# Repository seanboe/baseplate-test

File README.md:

# Baseplate test board

This is the baseplate test board for the Onyx baseplate. The schematic is mainly completed, but the layout isn't anywhere close to being finished. The board is based on the USB5537B 1-7 usb hub chip. 

Schematic:

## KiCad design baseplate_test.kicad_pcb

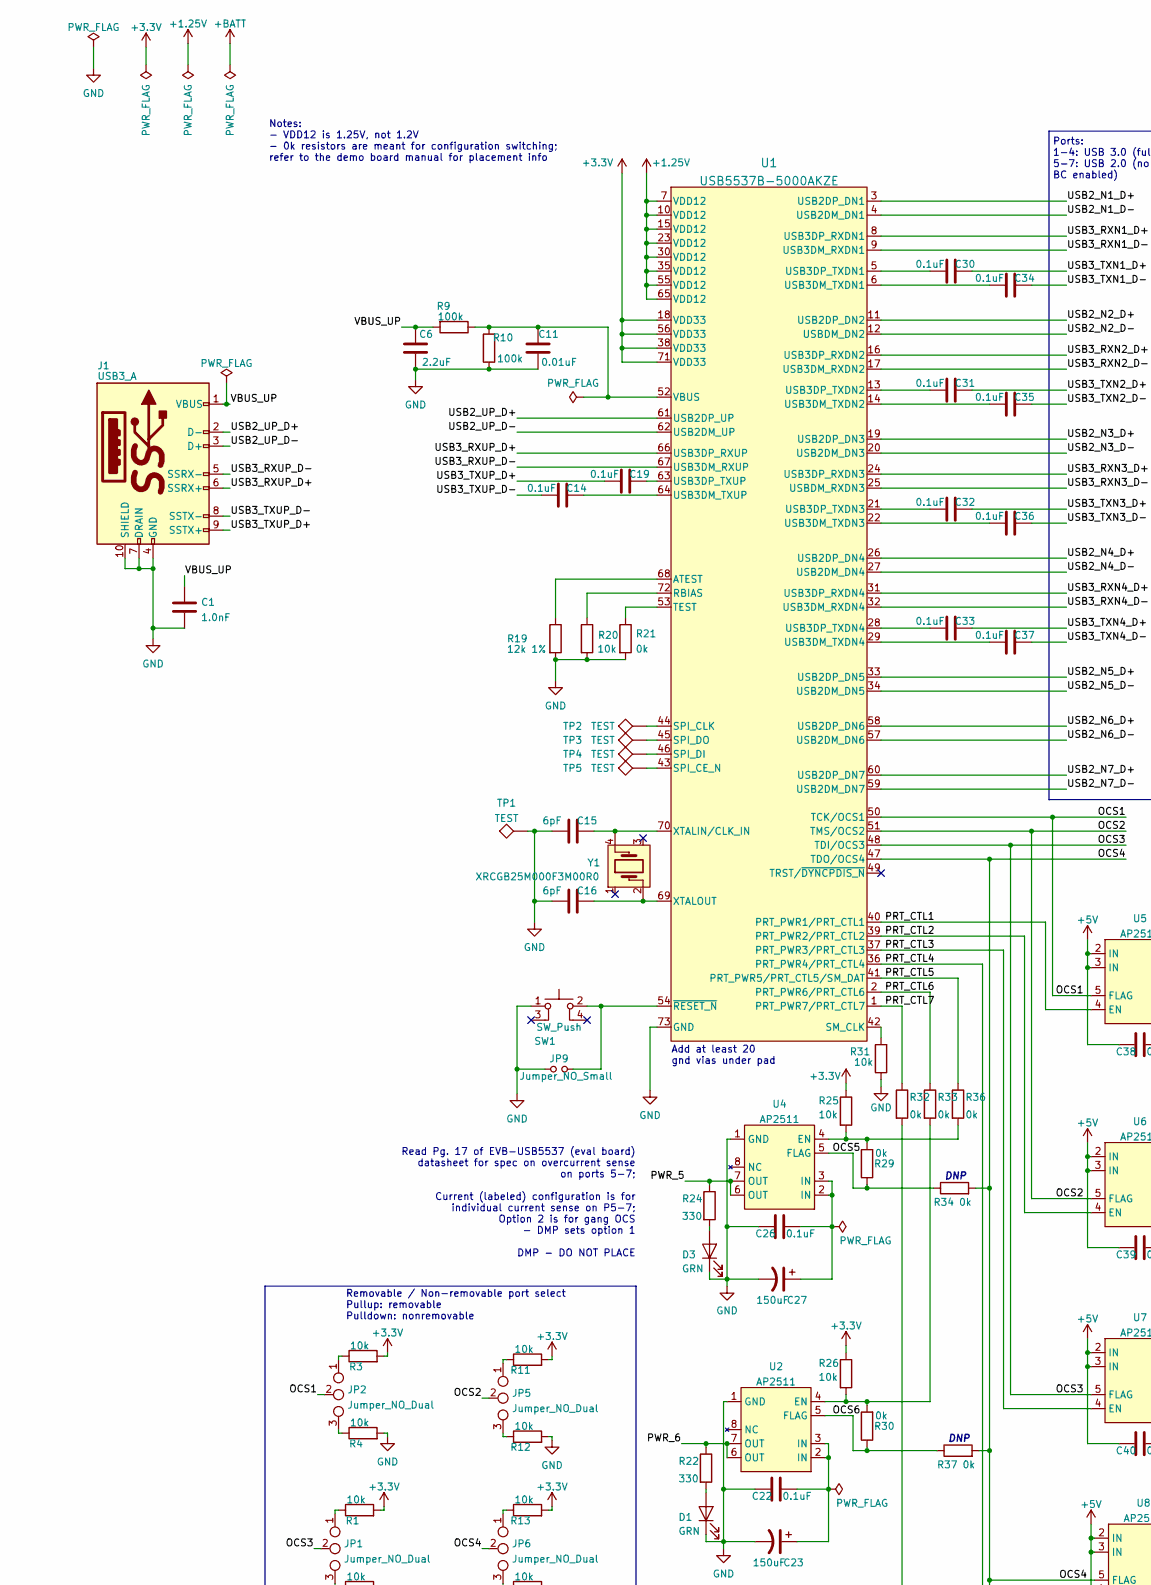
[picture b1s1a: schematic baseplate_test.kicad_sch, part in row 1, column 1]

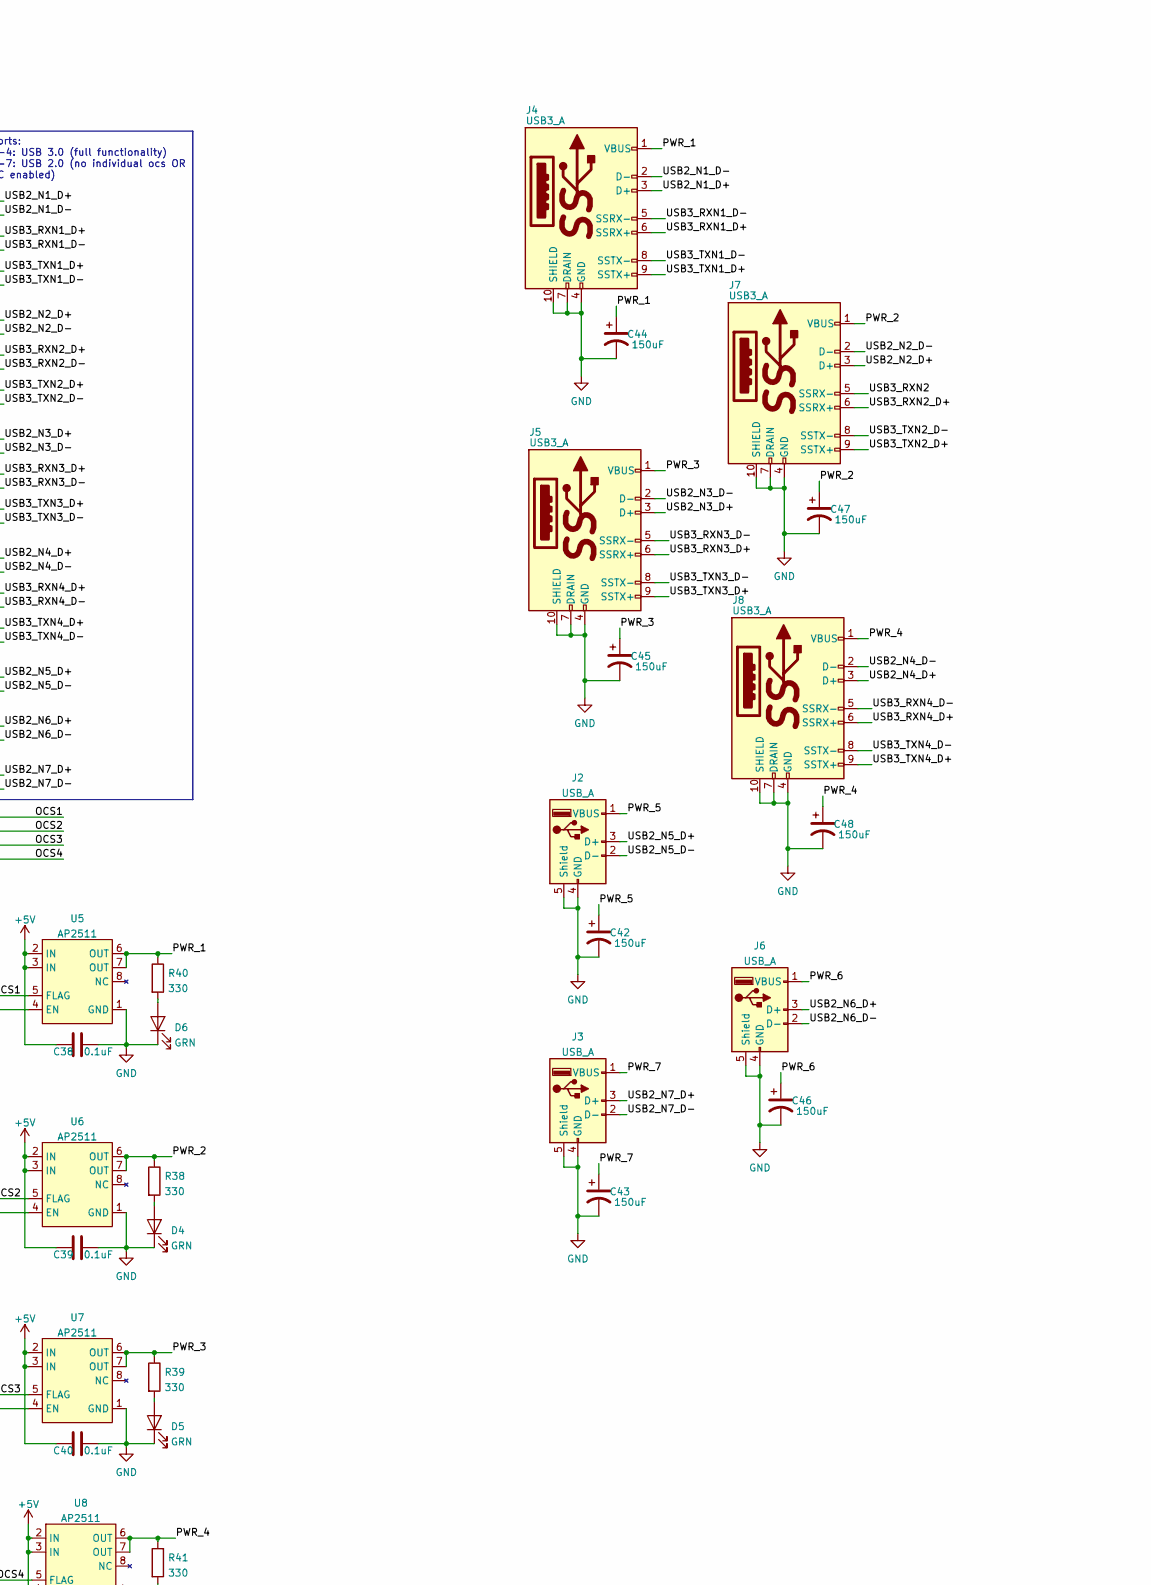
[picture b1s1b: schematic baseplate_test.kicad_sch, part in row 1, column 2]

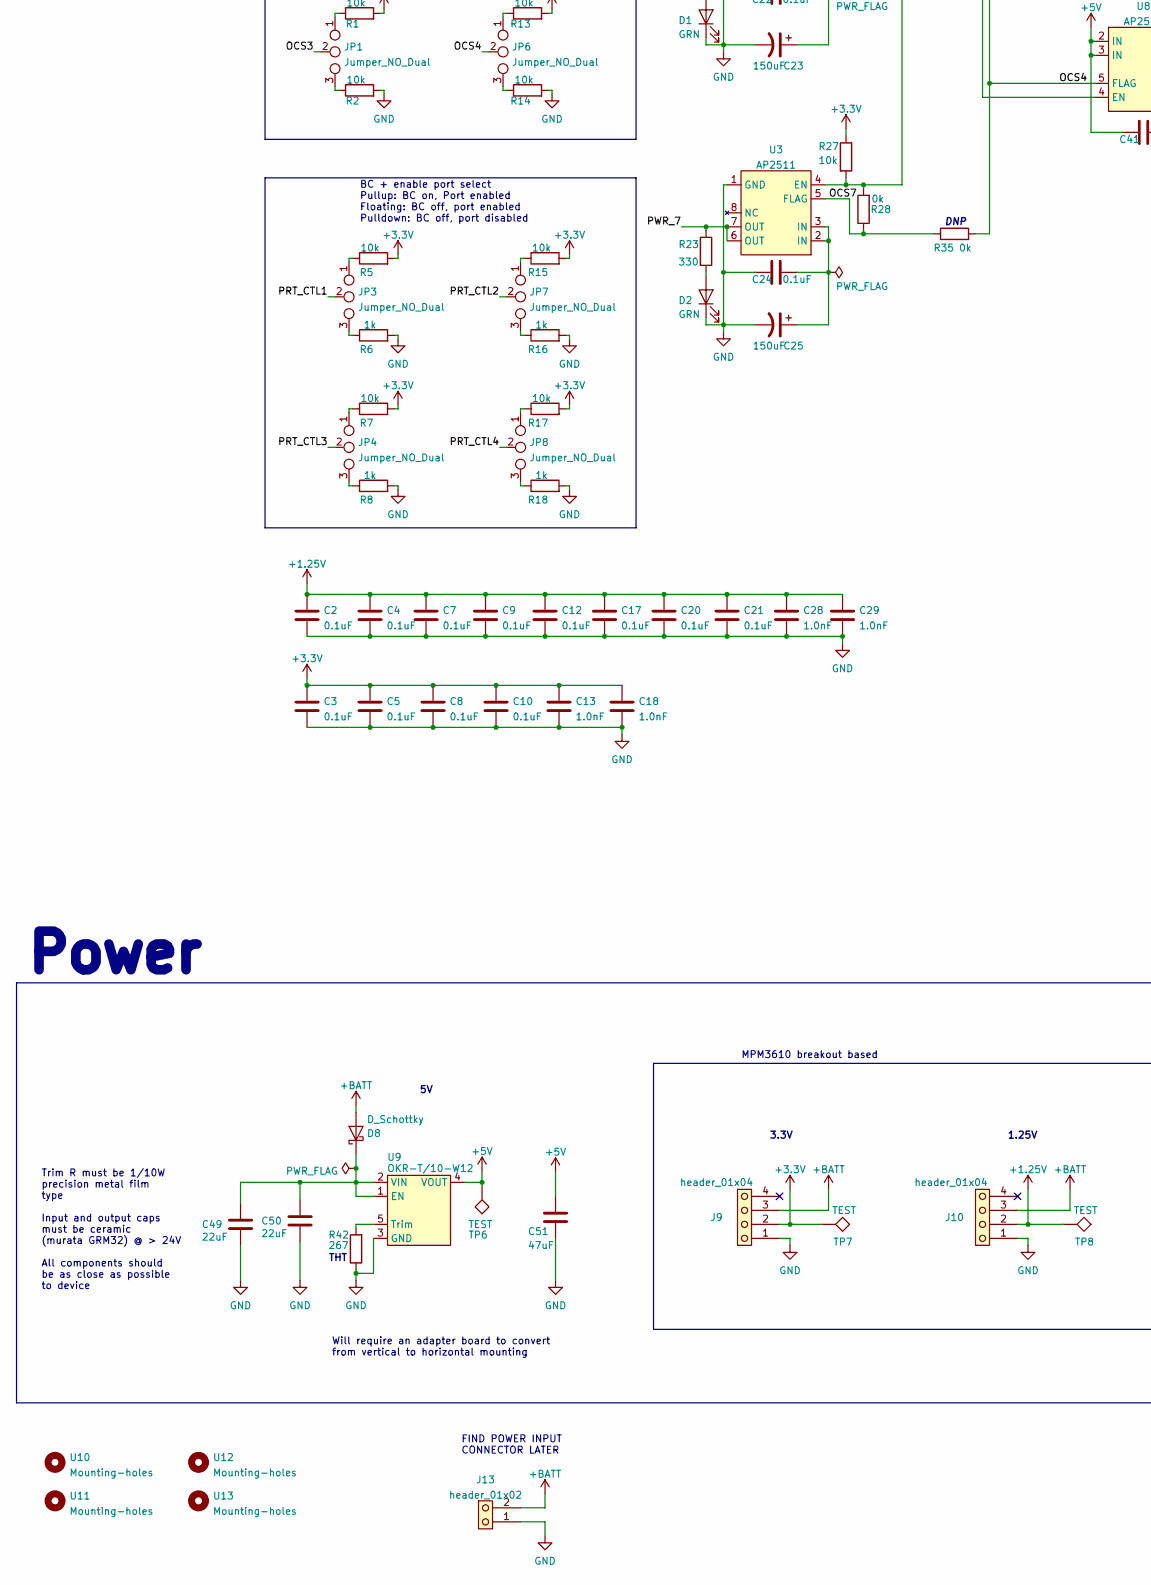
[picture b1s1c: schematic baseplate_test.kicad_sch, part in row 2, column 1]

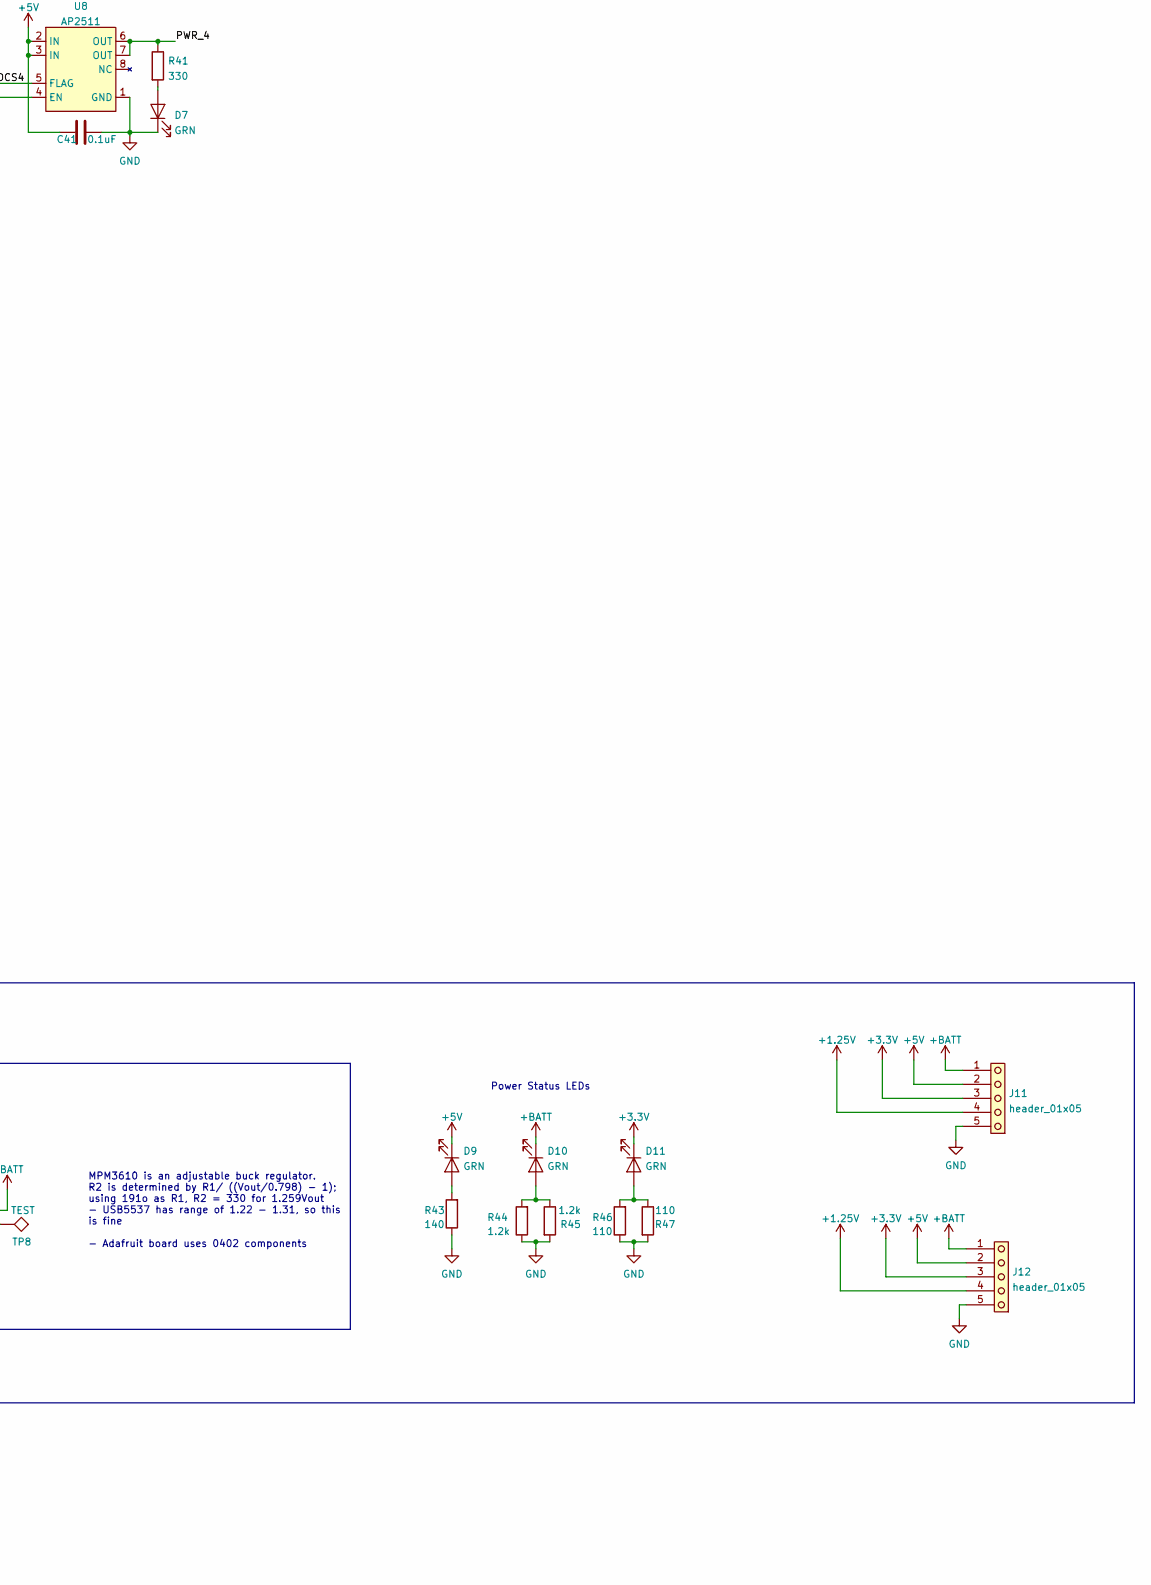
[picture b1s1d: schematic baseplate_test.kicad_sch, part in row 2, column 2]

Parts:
C1, C13, C18, C28, C29: 1.0nF; C_2012_805_A
C2, C3, C4, C5, C7, C8, C9, C10, C12, C14, C17, C19, C20, C21, C22, C24, C26, C30, C31, C32, C33, C34, C35, C36, C37, C38, C39, C40, C41: 0.1uF; C_1005_402_A
C6: 2.2uF; C_1608_603_A
C11: 0.01uF; C_1608_603_A
C15, C16: 6pF; C_1608_603_A
C23, C25, C27, C42, C43, C44, C45, C46, C47, C48: 150uF; EMZR100ARA151ME61G
C49, C50: 22uF; C_2012_805_A
C51: 47uF; C_2012_805_A
D1, D2, D3, D4, D5, D6, D7, D9, D10, D11: GRN; D_0805
D8: D_Schottky; MBR1560STR
J1, J4, J5, J7, J8: USB3_A; USB3_A_Molex_48393-001
J2, J3, J6: USB_A; USB_A_Molex_67643_Horizontal
J9, J10: header_01x04; header_01x04_pitch2.54_tht
J11, J12: header_01x05; header_01x05_pitch2.54_tht
J13: header_01x02; AMASS_XT60-F_1x02_P7.20mm_Vertical
JP1, JP2, JP3, JP4, JP5, JP6, JP7, JP8: Jumper_NO_Dual; SolderJumper-3_P1.3mm_Open_RoundedPad1.0x1.5mm_NumberLabels
JP9: Jumper_NO_Small; SolderJumper-2_P1.3mm_Open_RoundedPad1.0x1.5mm_no-silk
R1, R2, R3, R4, R5, R7, R11, R12, R13, R14, R15, R17, R20, R25, R26, R27, R31: 10k; R_1608_603_A
R6, R8, R16, R18: 1k; R_1608_603_A
R9, R10: 100k; R_1608_603_A
R19: 12k 1%; R_1608_603_A
R21, R28, R29, R30, R32, R33, R34, R35, R36, R37: 0k; R_1608_603_A
R22, R23, R24, R38, R39, R40, R41: 330; R_1608_603_A
R42: 267; RN55E2670BRE6
R43: 140; R_2012_805_A
R44, R45: 1.2k; R_6332_2512_A
R46, R47: 110; R_2012_805_A
SW1: SW_Push; CK_PTS645_SMD
TP1, TP2, TP3, TP4, TP5, TP6, TP7, TP8: TEST; test_point_2mm_square
U1: USB5537B-5000AKZE
U2, U3, U4, U5, U6, U7, U8: AP2511; AP2511M8-13
U9: OKR-T/10-W12; OKR-T_10-W12
U10, U11, U12, U13: Mounting-holes; plated_hole_3.0x3.6mm
Y1: XRCGB25M000F3M00R0; OSC_XRCGB25M000F3M00R0

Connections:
+1.25V: C2.1, C4.1, C7.1, C9.1, C12.1, C17.1, C20.1, C21.1, C28.1, C29.1, J10.2, J11.4, J12.4, TP8.1, U1.7 (VDD12), U1.10 (VDD12), U1.15 (VDD12), U1.23 (VDD12), U1.30 (VDD12), U1.35 (VDD12), U1.55 (VDD12), U1.65 (VDD12)
+3V3: C3.1, C5.1, C8.1, C10.1, C13.1, C18.1, D11.1 (K), J9.2, J11.3, J12.3, R1.2, R3.2, R5.2, R7.2, R11.2, R13.2, R15.2, R17.2, R25.1, R26.1, R27.1, TP7.1, U1.18 (VDD33), U1.38 (VDD33), U1.56 (VDD33), U1.71 (VDD33)
+5V: C38.2, C39.2, C40.2, C41.2, C51.1, D9.1 (K), J11.2, J12.2, TP6.1, U5.2 (IN), U5.3 (IN), U6.2 (IN), U6.3 (IN), U7.2 (IN), U7.3 (IN), U8.2 (IN), U8.3 (IN), U9.4 (VOUT)
+BATT: D8.2 (A), D10.1 (K), J9.3, J10.3, J11.1, J12.1, J13.2
/OCS1: JP2.2, U1.50 (TCK/OCS1), U5.5 (FLAG)
/OCS2: JP5.2, U1.51 (TMS/OCS2), U6.5 (FLAG)
/OCS3: JP1.2, U1.48 (TDI/OCS3), U7.5 (FLAG)
/OCS4: JP6.2, R34.2, R35.2, R37.2, U1.47 (TDO/OCS4), U8.5 (FLAG)
/OCS5: R29.1, R34.1, U4.5 (FLAG)
/OCS6: R30.1, R37.1, U2.5 (FLAG)
/OCS7: R28.1, R35.1, U3.5 (FLAG)
/PRT_CTL1: JP3.2, U1.40 (PRT_PWR1/PRT_CTL1), U5.4 (EN)
/PRT_CTL2: JP7.2, U1.39 (PRT_PWR2/PRT_CTL2), U6.4 (EN)
/PRT_CTL3: JP4.2, U1.37 (PRT_PWR3/PRT_CTL3), U7.4 (EN)
/PRT_CTL4: JP8.2, U1.36 (PRT_PWR4/PRT_CTL4), U8.4 (EN)
/PRT_CTL5: R36.1, U1.41 (PRT_PWR5/PRT_CTL5/SM_DAT)
/PRT_CTL6: R33.1, U1.2 (PRT_PWR6/PRT_CTL6)
/PRT_CTL7: R32.1, U1.1 (PRT_PWR7/PRT_CTL7)
/PWR_1: C44.1, J4.1 (VBUS), R40.1, U5.6 (OUT), U5.7 (OUT)
/PWR_2: C47.1, J7.1 (VBUS), R38.1, U6.6 (OUT), U6.7 (OUT)
/PWR_3: C45.1, J5.1 (VBUS), R39.1, U7.6 (OUT), U7.7 (OUT)
/PWR_4: C48.1, J8.1 (VBUS), R41.1, U8.6 (OUT), U8.7 (OUT)
/PWR_5: C42.1, J2.1 (VBUS), R24.1, U4.6 (OUT), U4.7 (OUT)
/PWR_6: C46.1, J6.1 (VBUS), R22.1, U2.6 (OUT), U2.7 (OUT)
/PWR_7: C43.1, J3.1 (VBUS), R23.1, U3.6 (OUT), U3.7 (OUT)
/USB2DM_N1: J4.2 (D-), U1.4 (USB2DM_DN1)
/USB2DM_N2: J7.2 (D-), U1.12 (USBDM_DN2)
/USB2DM_N3: J5.2 (D-), U1.20 (USB2DM_DN3)
/USB2DM_N4: J8.2 (D-), U1.27 (USB2DM_DN4)
/USB2DM_N5: J2.2 (D-), U1.34 (USB2DM_DN5)
/USB2DM_N6: J6.2 (D-), U1.57 (USB2DM_DN6)
/USB2DM_N7: J3.2 (D-), U1.59 (USB2DM_DN7)
/USB2DP_N1: J4.3 (D+), U1.3 (USB2DP_DN1)
/USB2DP_N2: J7.3 (D+), U1.11 (USB2DP_DN2)
/USB2DP_N3: J5.3 (D+), U1.19 (USB2DP_DN3)
/USB2DP_N4: J8.3 (D+), U1.26 (USB2DP_DN4)
/USB2DP_N5: J2.3 (D+), U1.33 (USB2DP_DN5)
/USB2DP_N6: J6.3 (D+), U1.58 (USB2DP_DN6)
/USB2DP_N7: J3.3 (D+), U1.60 (USB2DP_DN7)
/USB2_UP_D+: J1.2 (D-), U1.61 (USB2DP_UP)
/USB2_UP_D-: J1.3 (D+), U1.62 (USB2DM_UP)
/USB3DM_RXN1: J4.5 (SSRX-), U1.9 (USB3DM_RXDN1)
/USB3DM_RXN3: J5.5 (SSRX-), U1.25 (USBDM_RXDN3)
/USB3DM_RXN4: J8.5 (SSRX-), U1.32 (USB3DM_RXDN4)
/USB3DM_TXN1: C34.2, J4.8 (SSTX-)
/USB3DM_TXN2: C35.2, J7.8 (SSTX-)
/USB3DM_TXN3: C36.2, J5.8 (SSTX-)
/USB3DM_TXN4: C37.2, J8.8 (SSTX-)
/USB3DP_RXN1: J4.6 (SSRX+), U1.8 (USB3DP_RXDN1)
/USB3DP_RXN2: J7.6 (SSRX+), U1.16 (USB3DP_RXDN2)
/USB3DP_RXN3: J5.6 (SSRX+), U1.24 (USB3DP_RXDN3)
/USB3DP_RXN4: J8.6 (SSRX+), U1.31 (USB3DP_RXDN4)
/USB3DP_TXN1: C30.2, J4.9 (SSTX+)
/USB3DP_TXN2: C31.2, J7.9 (SSTX+)
/USB3DP_TXN3: C32.2, J5.9 (SSTX+)
/USB3DP_TXN4: C33.2, J8.9 (SSTX+)
/USB3_RXUP_D+: J1.6 (SSRX+), U1.66 (USB3DP_RXUP)
/USB3_RXUP_D-: J1.5 (SSRX-), U1.67 (USB3DM_RXUP)
/USB3_TXUP_D+: C19.1, J1.9 (SSTX+)
/USB3_TXUP_D-: C14.1, J1.8 (SSTX-)
/VBUS_UP: C1.1, C6.2, J1.1 (VBUS), R9.2
GND: C1.2, C2.2, C3.2, C4.2, C5.2, C6.1, C7.2, C8.2, C9.2, C10.2, C11.1, C12.2, C13.2, C15.1, C16.1, C17.2, C18.2, C20.2, C21.2, C22.2, C23.2, C24.2, C25.2, C26.2, C27.2, C28.2, C29.2, C38.1, C39.1, C40.1, C41.1, C42.2, C43.2, C44.2, C45.2, C46.2, C47.2, C48.2, C49.2, C50.2, C51.2, D1.1 (K), D2.1 (K), D3.1 (K), D4.1 (K), D5.1 (K), D6.1 (K), D7.1 (K), J1.4 (GND), J1.7 (DRAIN), J1.10 (SHIELD), J2.4 (GND), J2.5 (Shield), J3.4 (GND), J3.5 (Shield), J4.4 (GND), J4.7 (DRAIN), J4.10 (SHIELD), J5.4 (GND), J5.7 (DRAIN), J5.10 (SHIELD), J6.4 (GND), J6.5 (Shield), J7.4 (GND), J7.7 (DRAIN), J7.10 (SHIELD), J8.4 (GND), J8.7 (DRAIN), J8.10 (SHIELD), J9.1, J10.1, J11.5, J12.5, J13.1, JP9.1, R2.2, R4.2, R6.2, R8.2, R10.1, R12.2, R14.2, R16.2, R18.2, R19.2, R20.2, R21.2, R31.1, R42.1, R43.1, R44.1, R45.2, R46.1, R47.2, SW1.1, TP1.1, U1.73 (GND), U2.1 (GND), U3.1 (GND), U4.1 (GND), U5.1 (GND), U6.1 (GND), U7.1 (GND), U8.1 (GND), U9.3 (GND)
unnamed: C11.2, R9.1, R10.2, U1.52 (VBUS)
unnamed: C14.2, U1.64 (USB3DM_TXUP)
unnamed: C15.2, U1.70 (XTALIN/CLK_IN), Y1.4
unnamed: C16.2, U1.69 (XTALOUT), Y1.2
unnamed: C19.2, U1.63 (USB3DP_TXUP)
unnamed: C22.1, C23.1, U2.2 (IN), U2.3 (IN)
unnamed: C24.1, C25.1, U3.2 (IN), U3.3 (IN)
unnamed: C26.1, C27.1, U4.2 (IN), U4.3 (IN)
unnamed: C30.1, U1.5 (USB3DP_TXDN1)
unnamed: C31.1, U1.13 (USB3DP_TXDN2)
unnamed: C32.1, U1.21 (USB3DP_TXDN3)
unnamed: C33.1, U1.28 (USB3DP_TXDN4)
unnamed: C34.1, U1.6 (USB3DM_TXDN1)
unnamed: C35.1, U1.14 (USB3DM_TXDN2)
unnamed: C36.1, U1.22 (USB3DM_TXDN3)
unnamed: C37.1, U1.29 (USB3DM_TXDN4)
unnamed: C49.1, C50.1, D8.1 (K), U9.1 (EN), U9.2 (VIN)
unnamed: D1.2 (A), R22.2
unnamed: D2.2 (A), R23.2
unnamed: D3.2 (A), R24.2
unnamed: D4.2 (A), R38.2
unnamed: D5.2 (A), R39.2
unnamed: D6.2 (A), R40.2
unnamed: D7.2 (A), R41.2
unnamed: D9.2 (A), R43.2
unnamed: D10.2 (A), R44.2, R45.1
unnamed: D11.2 (A), R46.2, R47.1
unnamed: JP1.1, R1.1
unnamed: JP1.3, R2.1
unnamed: JP2.1, R3.1
unnamed: JP2.3, R4.1
unnamed: JP3.1, R5.1
unnamed: JP3.3, R6.1
unnamed: JP4.1, R7.1
unnamed: JP4.3, R8.1
unnamed: JP5.1, R11.1
unnamed: JP5.3, R12.1
unnamed: JP6.1, R13.1
unnamed: JP6.3, R14.1
unnamed: JP7.1, R15.1
unnamed: JP7.3, R16.1
unnamed: JP8.1, R17.1
unnamed: JP8.3, R18.1
unnamed: JP9.2, SW1.2, U1.54 (~RESET_N)
unnamed: R19.1, U1.68 (ATEST)
unnamed: R20.1, U1.72 (RBIAS)
unnamed: R21.1, U1.53 (TEST)
unnamed: R25.2, R29.2, R36.2, U4.4 (EN)
unnamed: R26.2, R30.2, R33.2, U2.4 (EN)
unnamed: R27.2, R28.2, R32.2, U3.4 (EN)
unnamed: R31.2, U1.42 (SM_CLK)
unnamed: R42.2, U9.5 (Trim)
unnamed: TP2.1, U1.44 (SPI_CLK)
unnamed: TP3.1, U1.45 (SPI_DO)
unnamed: TP4.1, U1.46 (SPI_DI)
unnamed: TP5.1, U1.43 (SPI_CE_N)

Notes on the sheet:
DNP
Notes: - VDD12 is 1.25V, not 1.2V - 0k resistors are meant for configuration switching; refer to the demo board manual for placement info
3.3V
MPM3610 is an adjustable buck regulator. R2 is determined by R1/ ((Vout/0.798) - 1); using 191o as R1, R2 = 330 for 1.259Vout - USB5537 has range of 1.22 - 1.31, so this is fine - Adafruit board uses 0402 components
MPM3610 breakout based
THT
BC + enable port select Pullup: BC on, Port enabled Floating: BC off, port enabled Pulldown: BC off, port disabled
Removable / Non-removable port select Pullup: removable Pulldown: nonremovable
Read Pg. 17 of EVB-USB5537 (eval board) datasheet for spec on overcurrent sense on ports 5-7; Current (labeled) configuration is for individual current sense on P5-7; Option 2 is for gang OCS - DMP sets option 1 DMP - DO NOT PLACE
Trim R must be 1/10W precision metal film type Input and output caps must be ceramic (murata GRM32) @ > 24V All components should be as close as possible to device
Will require an adapter board to convert from vertical to horizontal mounting
Power
FIND POWER INPUT CONNECTOR LATER
Power Status LEDs
Add at least 20 gnd vias under pad
Ports: 1-4: USB 3.0 (full functionality) 5-7: USB 2.0 (no individual ocs OR BC enabled)
1.25V

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
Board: 2 copper layers, 154 parts (0 on the bottom side), 119 nets, no tracks yet.

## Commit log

2022-03-21 stuff
2022-03-26 schematic finished (pretty much)
2022-06-24 most recent updates
